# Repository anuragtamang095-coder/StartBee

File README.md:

# STARBEE
HERE lies my project, Starbee a motion controlled digital pet.
for more information visit these:
Journal:  
BOM: 
images:

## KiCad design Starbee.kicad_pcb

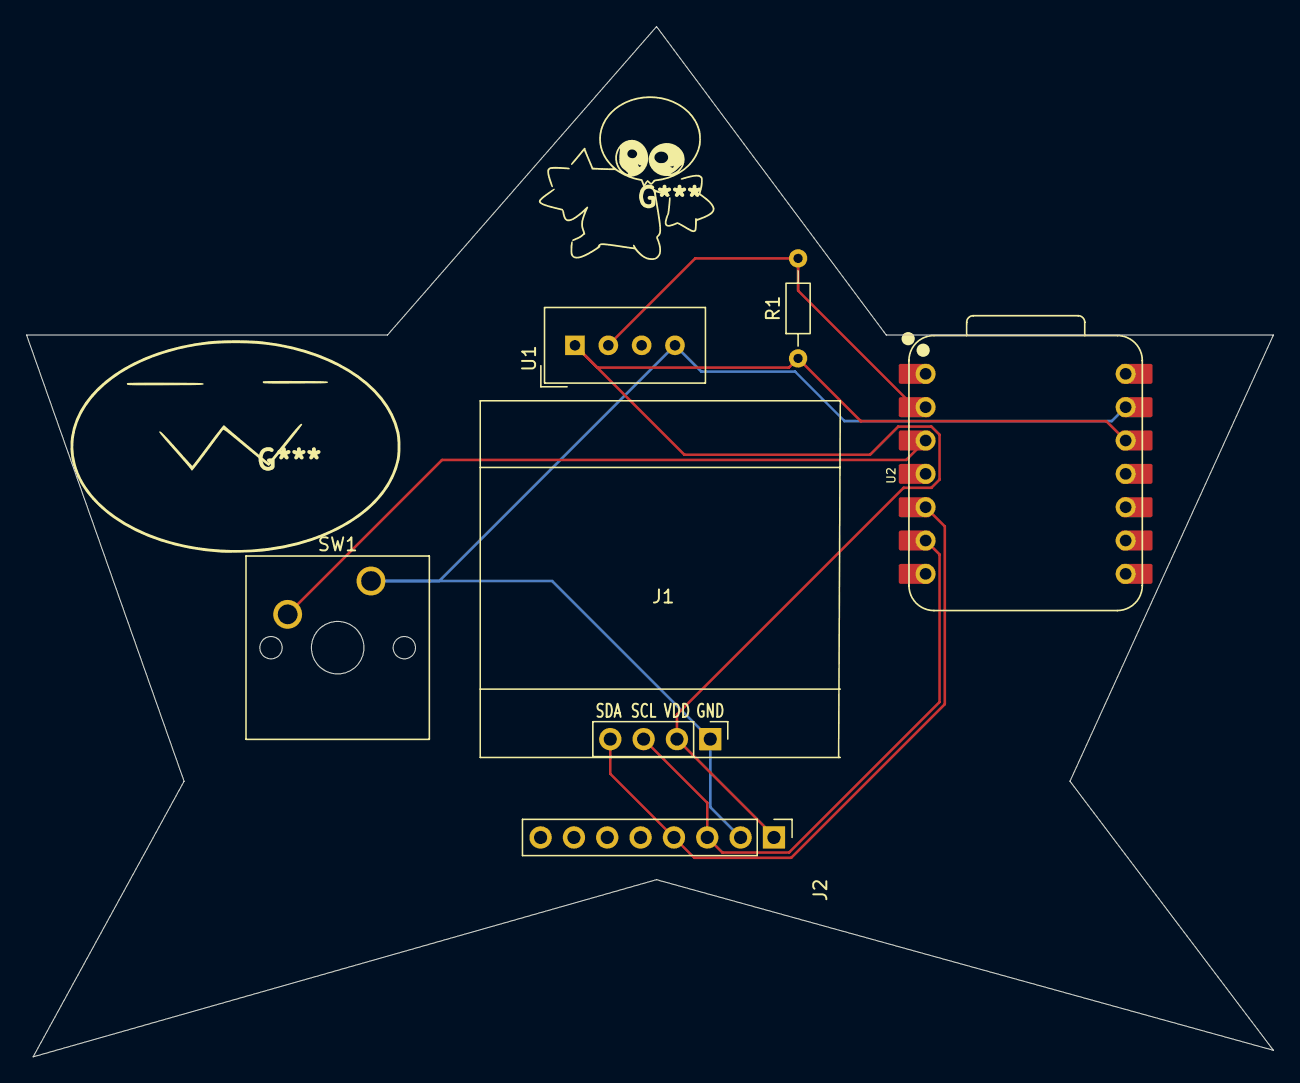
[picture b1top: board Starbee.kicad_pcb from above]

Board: 2 copper layers, 95.0 x 78.5 mm, 6 parts (0 on the bottom side), 6 nets.

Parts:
J1: Conn_01x04_Pin; Display_128x64_096_I2C
J2: Conn_01x08_Pin; PinHeader_1x08_P2.54mm_Vertical
R1: 10k; R_Axial_DIN0204_L3.6mm_D1.6mm_P7.62mm_Horizontal
SW1: SW_Push; SW_Cherry_MX_1.00u_PCB
U1: DHT11; Aosong_DHT11_5.5x12.0_P2.54mm
U2: XIAO-ESP32-C3-SMD; XIAO-ESP32-C6-DIP

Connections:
+3.3V: J1.2, J2.1, R1.1, U1.1 (VDD), U2.12 (3V3_OUT)
/DHT11 DATA: R1.2, U1.2 (DATA), U2.2 (D1)
/SCL: J1.3, J2.3, U2.6 (D5)
/SDA: J1.4, J2.4, U2.5 (D4)
GND: J1.1, J2.2, SW1.1, U1.4 (GND), U2.13 (GND)
unnamed: SW1.2, U2.3 (D2)
